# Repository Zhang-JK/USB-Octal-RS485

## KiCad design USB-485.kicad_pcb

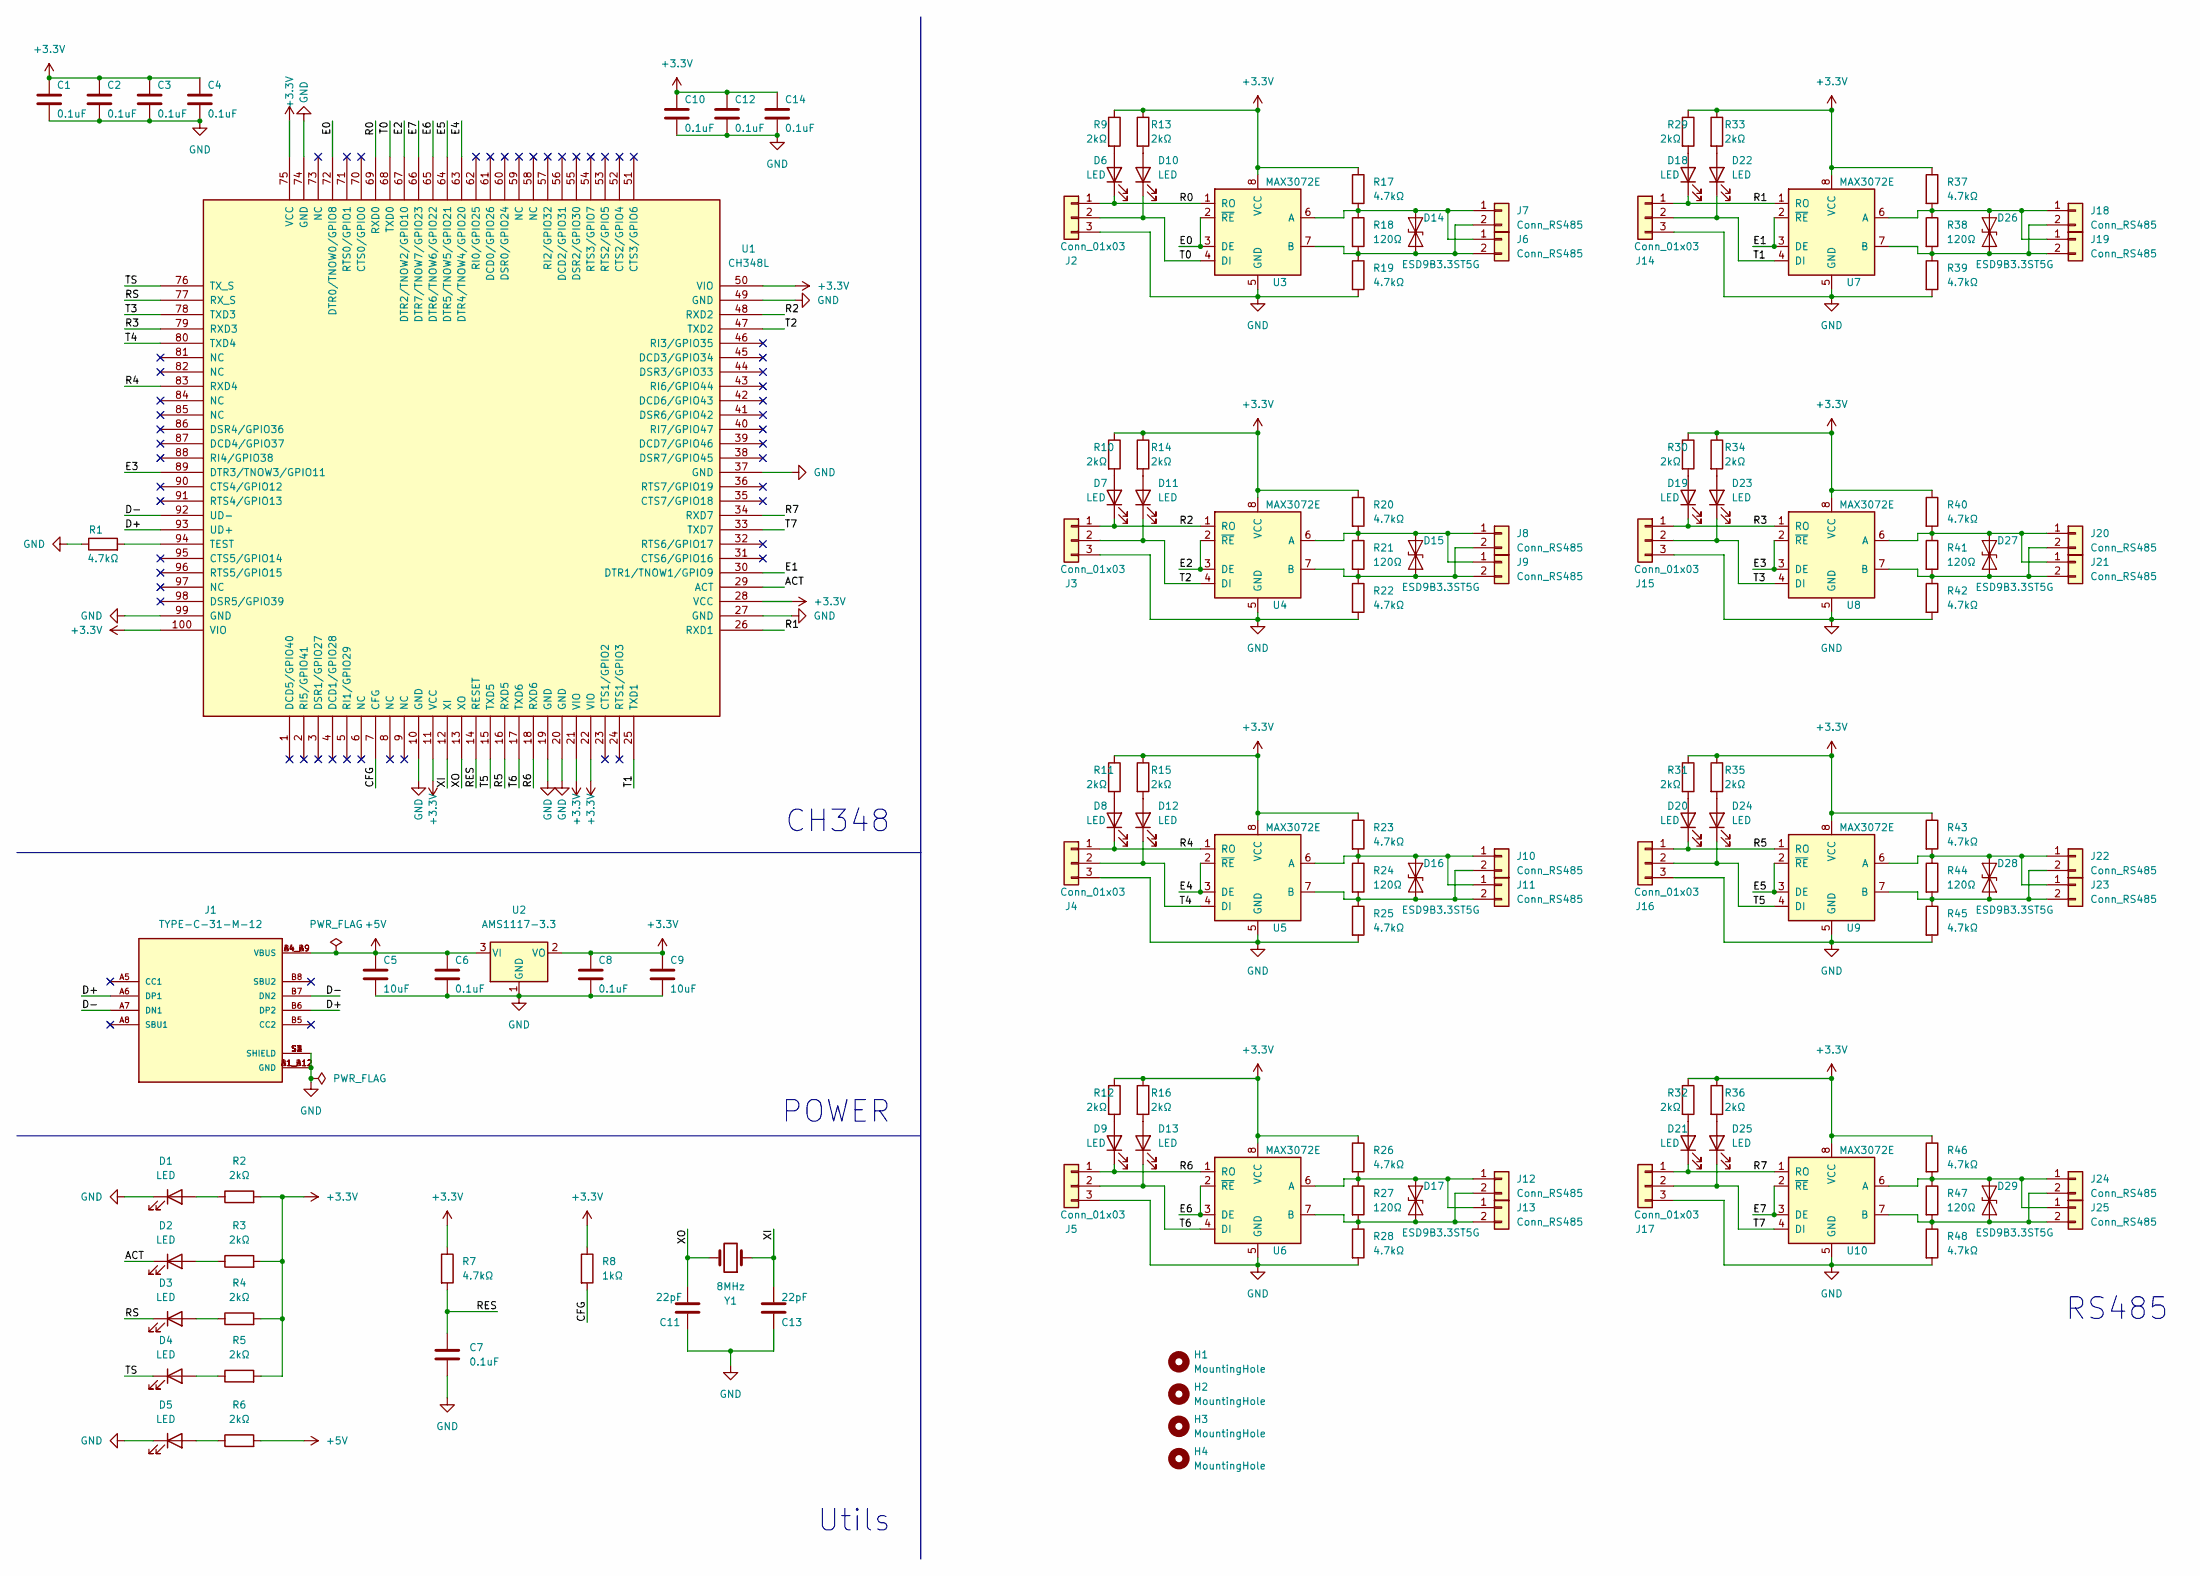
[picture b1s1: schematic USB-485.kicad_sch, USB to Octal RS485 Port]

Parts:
C1, C2, C3, C4, C6, C7, C8, C10, C12, C14: 0.1uF; C_0603_1608Metric
C5, C9: 10uF; C_0603_1608Metric
C11, C13: 22pF; C_0603_1608Metric
D1, D2, D3, D4, D5, D6, D7, D8, D9, D10, D11, D12, D13, D18, D19, D20, D21, D22, D23, D24, D25: LED; LED_0603_1608Metric
D14, D15, D16, D17, D26, D27, D28, D29: ESD9B3.3ST5G; D_SOD-923
H1, H2, H3, H4: MountingHole; MountingHole_2.7mm_M2.5_DIN965_Pad_TopBottom
J1: TYPE-C-31-M-12; HRO_TYPE-C-31-M-12; PARTREV 2020.12.08
J2, J3, J4, J5, J14, J15, J16, J17: Conn_01x03; JST_GH_SM03B-GHS-TB_1x03-1MP_P1.25mm_Horizontal
J6, J7, J8, J9, J10, J11, J12, J13, J18, J19, J20, J21, J22, J23, J24, J25: Conn_RS485; JST_GH_SM02B-GHS-TB_1x02-1MP_P1.25mm_Horizontal
R1, R7, R17, R19, R20, R22, R23, R25, R26, R28, R37, R39, R40, R42, R43, R45, R46, R48: 4.7kΩ; R_0603_1608Metric
R2, R3, R4, R5, R6, R9, R10, R11, R12, R13, R14, R15, R16, R29, R30, R31, R32, R33, R34, R35, R36: 2kΩ; R_0603_1608Metric
R8: 1kΩ; R_0603_1608Metric
R18, R21, R24, R27, R38, R41, R44, R47: 120Ω; R_0603_1608Metric
U1: CH348L; LQFP-100_14x14mm_P0.5mm
U2: AMS1117-3.3; SOT-223-3_TabPin2
U3, U4, U5, U6, U7, U8, U9, U10: MAX3072E; SOIC-8_3.9x4.9mm_P1.27mm
Y1: 8MHz; Crystal_SMD_Qantek_QC5CB-2Pin_5x3.2mm

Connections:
+3.3V: C1.1, C2.1, C3.1, C4.1, C8.1, C9.1, C10.1, C12.1, C14.1, R2.2, R3.2, R4.2, R5.2, R7.1, R8.1, R9.1, R10.1, R11.1, R12.1, R13.1, R14.1, R15.1, R16.1, R17.1, R20.1, R23.1, R26.1, R29.1, R30.1, R31.1, R32.1, R33.1, R34.1, R35.1, R36.1, R37.1, R40.1, R43.1, R46.1, U1.11 (VCC), U1.21 (VIO), U1.22 (VIO), U1.28 (VCC), U1.50 (VIO), U1.75 (VCC), U1.100 (VIO), U2.2 (VO), U3.8 (VCC), U4.8 (VCC), U5.8 (VCC), U6.8 (VCC), U7.8 (VCC), U8.8 (VCC), U9.8 (VCC), U10.8 (VCC)
+5V: C5.1, C6.1, J1.A4_B9 (VBUS), J1.B4_A9 (VBUS), R6.2, U2.3 (VI)
/ACT: D2.1 (K), U1.29 (ACT)
/CFG: R8.2, U1.7 (CFG)
/D+: J1.A6 (DP1), J1.B6 (DP2), U1.93 (UD+)
/D-: J1.A7 (DN1), J1.B7 (DN2), U1.92 (UD-)
/E0: U1.72 (DTR0/TNOW0/GPIO8), U3.2 (~RE), U3.3 (DE)
/E1: U1.30 (DTR1/TNOW1/GPIO9), U7.2 (~RE), U7.3 (DE)
/E2: U1.67 (DTR2/TNOW2/GPIO10), U4.2 (~RE), U4.3 (DE)
/E3: U1.89 (DTR3/TNOW3/GPIO11), U8.2 (~RE), U8.3 (DE)
/E4: U1.63 (DTR4/TNOW4/GPIO20), U5.2 (~RE), U5.3 (DE)
/E5: U1.64 (DTR5/TNOW5/GPIO21), U9.2 (~RE), U9.3 (DE)
/E6: U1.65 (DTR6/TNOW6/GPIO22), U6.2 (~RE), U6.3 (DE)
/E7: U1.66 (DTR7/TNOW7/GPIO23), U10.2 (~RE), U10.3 (DE)
/R0: D6.1 (K), J2.1, U1.69 (RXD0), U3.1 (RO)
/R1: D18.1 (K), J14.1, U1.26 (RXD1), U7.1 (RO)
/R2: D7.1 (K), J3.1, U1.48 (RXD2), U4.1 (RO)
/R3: D19.1 (K), J15.1, U1.79 (RXD3), U8.1 (RO)
/R4: D8.1 (K), J4.1, U1.83 (RXD4), U5.1 (RO)
/R5: D20.1 (K), J16.1, U1.16 (RXD5), U9.1 (RO)
/R6: D9.1 (K), J5.1, U1.18 (RXD6), U6.1 (RO)
/R7: D21.1 (K), J17.1, U1.34 (RXD7), U10.1 (RO)
/RES: C7.1, R7.2, U1.14 (RESET)
/RS: D3.1 (K), U1.77 (RX_S)
/T0: D10.1 (K), J2.2, U1.68 (TXD0), U3.4 (DI)
/T1: D22.1 (K), J14.2, U1.25 (TXD1), U7.4 (DI)
/T2: D11.1 (K), J3.2, U1.47 (TXD2), U4.4 (DI)
/T3: D23.1 (K), J15.2, U1.78 (TXD3), U8.4 (DI)
/T4: D12.1 (K), J4.2, U1.80 (TXD4), U5.4 (DI)
/T5: D24.1 (K), J16.2, U1.15 (TXD5), U9.4 (DI)
/T6: D13.1 (K), J5.2, U1.17 (TXD6), U6.4 (DI)
/T7: D25.1 (K), J17.2, U1.33 (TXD7), U10.4 (DI)
/TS: D4.1 (K), U1.76 (TX_S)
/XI: C13.2, U1.12 (XI), Y1.1
/XO: C11.2, U1.13 (XO), Y1.2
GND: C1.2, C2.2, C3.2, C4.2, C5.2, C6.2, C7.2, C8.2, C9.2, C10.2, C11.1, C12.2, C13.1, C14.2, D1.1 (K), D5.1 (K), J1.A1_B12 (GND), J1.B1_A12 (GND), J1.S1 (SHIELD), J1.S2 (SHIELD), J1.S3 (SHIELD), J1.S4 (SHIELD), J2.3, J3.3, J4.3, J5.3, J14.3, J15.3, J16.3, J17.3, R1.1, R19.2, R22.2, R25.2, R28.2, R39.2, R42.2, R45.2, R48.2, U1.10 (GND), U1.19 (GND), U1.20 (GND), U1.27 (GND), U1.37 (GND), U1.49 (GND), U1.74 (GND), U1.99 (GND), U2.1 (GND), U3.5 (GND), U4.5 (GND), U5.5 (GND), U6.5 (GND), U7.5 (GND), U8.5 (GND), U9.5 (GND), U10.5 (GND)
unnamed: D1.2 (A), R2.1
unnamed: D2.2 (A), R3.1
unnamed: D3.2 (A), R4.1
unnamed: D4.2 (A), R5.1
unnamed: D5.2 (A), R6.1
unnamed: D6.2 (A), R9.2
unnamed: D7.2 (A), R10.2
unnamed: D8.2 (A), R11.2
unnamed: D9.2 (A), R12.2
unnamed: D10.2 (A), R13.2
unnamed: D11.2 (A), R14.2
unnamed: D12.2 (A), R15.2
unnamed: D13.2 (A), R16.2
unnamed: D14.1 (A1), J6.2, J7.2, R18.2, R19.1, U3.7 (B)
unnamed: D14.2 (A2), J6.1, J7.1, R17.2, R18.1, U3.6 (A)
unnamed: D15.1 (A1), J8.2, J9.2, R21.2, R22.1, U4.7 (B)
unnamed: D15.2 (A2), J8.1, J9.1, R20.2, R21.1, U4.6 (A)
unnamed: D16.1 (A1), J10.2, J11.2, R24.2, R25.1, U5.7 (B)
unnamed: D16.2 (A2), J10.1, J11.1, R23.2, R24.1, U5.6 (A)
unnamed: D17.1 (A1), J12.2, J13.2, R27.2, R28.1, U6.7 (B)
unnamed: D17.2 (A2), J12.1, J13.1, R26.2, R27.1, U6.6 (A)
unnamed: D18.2 (A), R29.2
unnamed: D19.2 (A), R30.2
unnamed: D20.2 (A), R31.2
unnamed: D21.2 (A), R32.2
unnamed: D22.2 (A), R33.2
unnamed: D23.2 (A), R34.2
unnamed: D24.2 (A), R35.2
unnamed: D25.2 (A), R36.2
unnamed: D26.1 (A1), J18.2, J19.2, R38.2, R39.1, U7.7 (B)
unnamed: D26.2 (A2), J18.1, J19.1, R37.2, R38.1, U7.6 (A)
unnamed: D27.1 (A1), J20.2, J21.2, R41.2, R42.1, U8.7 (B)
unnamed: D27.2 (A2), J20.1, J21.1, R40.2, R41.1, U8.6 (A)
unnamed: D28.1 (A1), J22.2, J23.2, R44.2, R45.1, U9.7 (B)
unnamed: D28.2 (A2), J22.1, J23.1, R43.2, R44.1, U9.6 (A)
unnamed: D29.1 (A1), J24.2, J25.2, R47.2, R48.1, U10.7 (B)
unnamed: D29.2 (A2), J24.1, J25.1, R46.2, R47.1, U10.6 (A)
unnamed: R1.2, U1.94 (TEST)

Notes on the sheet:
RS485
Utils
CH348
POWER

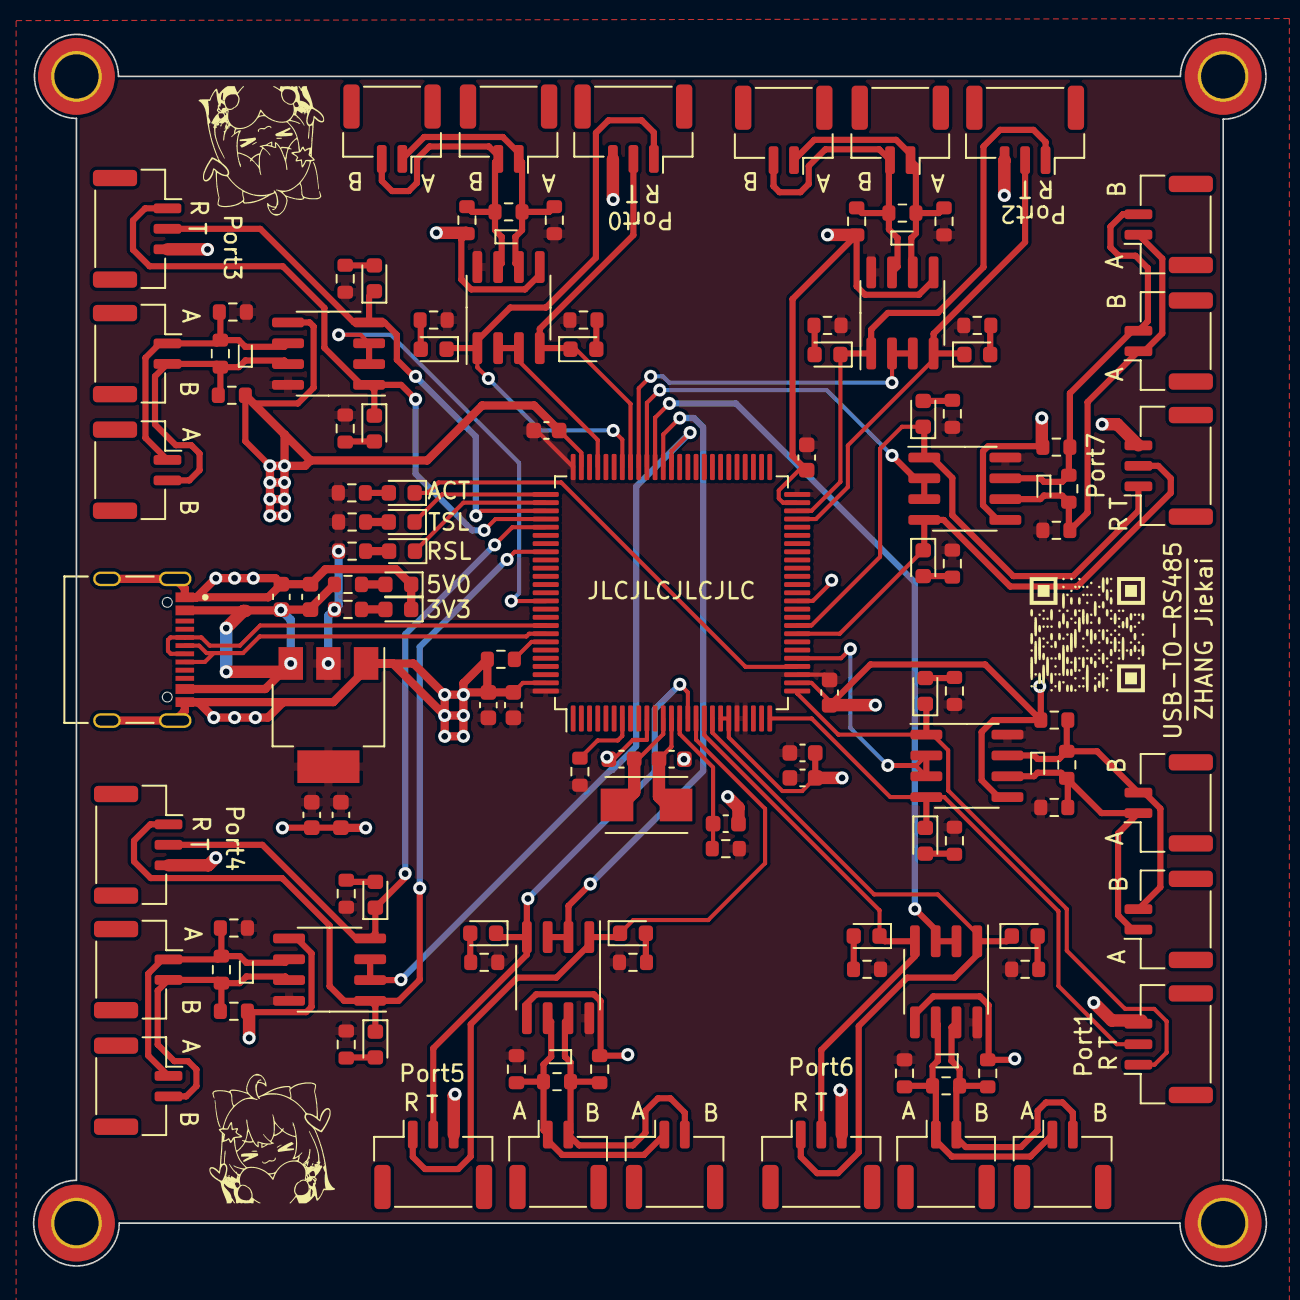
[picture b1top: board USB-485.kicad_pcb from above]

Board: 2 copper layers, 75.3 x 75.3 mm, 131 parts (0 on the bottom side), 74 nets.

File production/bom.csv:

Designator,Footprint,Quantity,Value,LCSC Part #
"C1, C10, C12, C14, C2, C3, C4, C6, C7, C8",C_0603_1608Metric,10,0.1uF,
"C11, C13",C_0603_1608Metric,2,22pF,
"C5, C9",C_0603_1608Metric,2,10uF,
"D1, D10, D11, D12, D13, D18, D19, D2, D20, D21, D22, D23, D24, D25, D3, D4, D5, D6, D7, D8, D9",LED_0603_1608Metric,21,LED,
"D14, D15, D16, D17, D26, D27, D28, D29",D_SOD-923,8,ESD9B3.3ST5G,
"H1, H2, H3, H4",MountingHole_2.7mm_M2.5_DIN965_Pad_TopBottom,4,MountingHole,
J1,HRO_TYPE-C-31-M-12,1,TYPE-C-31-M-12,
"J10, J11, J12, J13, J18, J19, J20, J21, J22, J23, J24, J25, J6, J7, J8, J9",JST_GH_SM02B-GHS-TB_1x02-1MP_P1.25mm_Horizontal,16,Conn_RS485,
"J14, J15, J16, J17, J2, J3, J4, J5",JST_GH_SM03B-GHS-TB_1x03-1MP_P1.25mm_Horizontal,8,Conn_01x03,
"R1, R17, R19, R20, R22, R23, R25, R26, R28, R37, R39, R40, R42, R43, R45, R46, R48, R7",R_0603_1608Metric,18,4.7kΩ,
"R10, R11, R12, R13, R14, R15, R16, R2, R29, R3, R30, R31, R32, R33, R34, R35, R36, R4, R5, R6, R9",R_0603_1608Metric,21,2kΩ,
"R18, R21, R24, R27, R38, R41, R44, R47",R_0603_1608Metric,8,120Ω,
R8,R_0603_1608Metric,1,1kΩ,
U1,LQFP-100_14x14mm_P0.5mm,1,CH348L,
"U10, U3, U4, U5, U6, U7, U8, U9",SOIC-8_3.9x4.9mm_P1.27mm,8,MAX3072E,
U2,SOT-223-3_TabPin2,1,AMS1117-3.3,
Y1,Crystal_SMD_Qantek_QC5CB-2Pin_5x3.2mm,1,8MHz,

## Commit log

2023-01-11 add board files
2023-01-11 add testing file
2023-01-11 add adriver and datasheer
2023-01-17 add test for RMD motors
